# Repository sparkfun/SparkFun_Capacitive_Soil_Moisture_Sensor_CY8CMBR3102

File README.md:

[*SparkFun Qwiic Soil Moisture Sensor (Capacitive) (SEN-30480)*](https://www.sparkfun.com/sparkfun-qwiic-soil-moisture-sensor-capacitive.html)

The SparkFun Qwiic Soil Moisture Sensor (Capacative) is a simple sensor breakout to measure moisture in soil and similar substances. The breakout measures moisture using a capacitive plate in the board along with the CY8CMBR3102 Capsense<sup>&reg;</sup> Express<sup>&trade;</sup> controller. Because this soil moisture sensor does not have exposed metal leads it's more resistant to corrosion. The board also includes a ruler with both Imperial and Metric units to measure the sensor's depth in soil for more precise moisture data. There's also a blue status LED tied to the CY8CMBR3102 which can be used as a visual indicator for when the sensor measures beyond a user-defined threshold value.

The SparkFun Qwiic Soil Moisture Sensor (Capacative) has code packages available for both the Arduino IDE and MicroPython. These code packages cover how to calibrate the sensor for different soil compositions to get reliable and usable soil moisture data from the sensor.

Repository Contents
-------------------

* **/docs** - GitHub pages documentation files
* **/Documentation** - Datasheets, etc. 
* **/Hardware** - KiCad design files (_pcb, _sch), Schematic (PDF)
* **/Production** - Production panel files (_pcb, gerbers)

Documentation
--------------
* [**Arduino Library**](https://github.com/sparkfun/SparkFun_CY8CMBR3_Arduino_Library) - Arduino library for CY8CMBR3xxx capacitance sensors, specifically for the Qwiic Soil Moisture Sensor (Capacitive).
* [**Python Package**](https://github.com/sparkfun/qwiic_cy8cmbr3_py) - A Python driver for CY8CMBR3xxx capacitance sensors, specifically for the Qwiic Soil Moisture Sensor (Capacitive).
* [**Hookup Guide**](https://docs.sparkfun.com/SparkFun_Capacitive_Soil_Moisture_Sensor_CY8CMBR3102/introduction/) - A basic guide to get started with the Qwiic Soil Moisture Sensor (Capacitive)

Product Versions
-----------------

* [SEN-30480](https://www.sparkfun.com/sparkfun-qwiic-soil-moisture-sensor-capacitive.html) - Initial SparkFun Qwiic Soil Moisture Sensor (Capacitive) release.

License Information
-------------------

This product is _**open source**_! 

Please review the LICENSE.md file for license information. 

If you have any questions or concerns on licensing, please contact technical support on our [SparkFun forums](https://forum.sparkfun.com/viewforum.php?f=152).

Distributed as-is; no warranty is given.

- Your friends at SparkFun.

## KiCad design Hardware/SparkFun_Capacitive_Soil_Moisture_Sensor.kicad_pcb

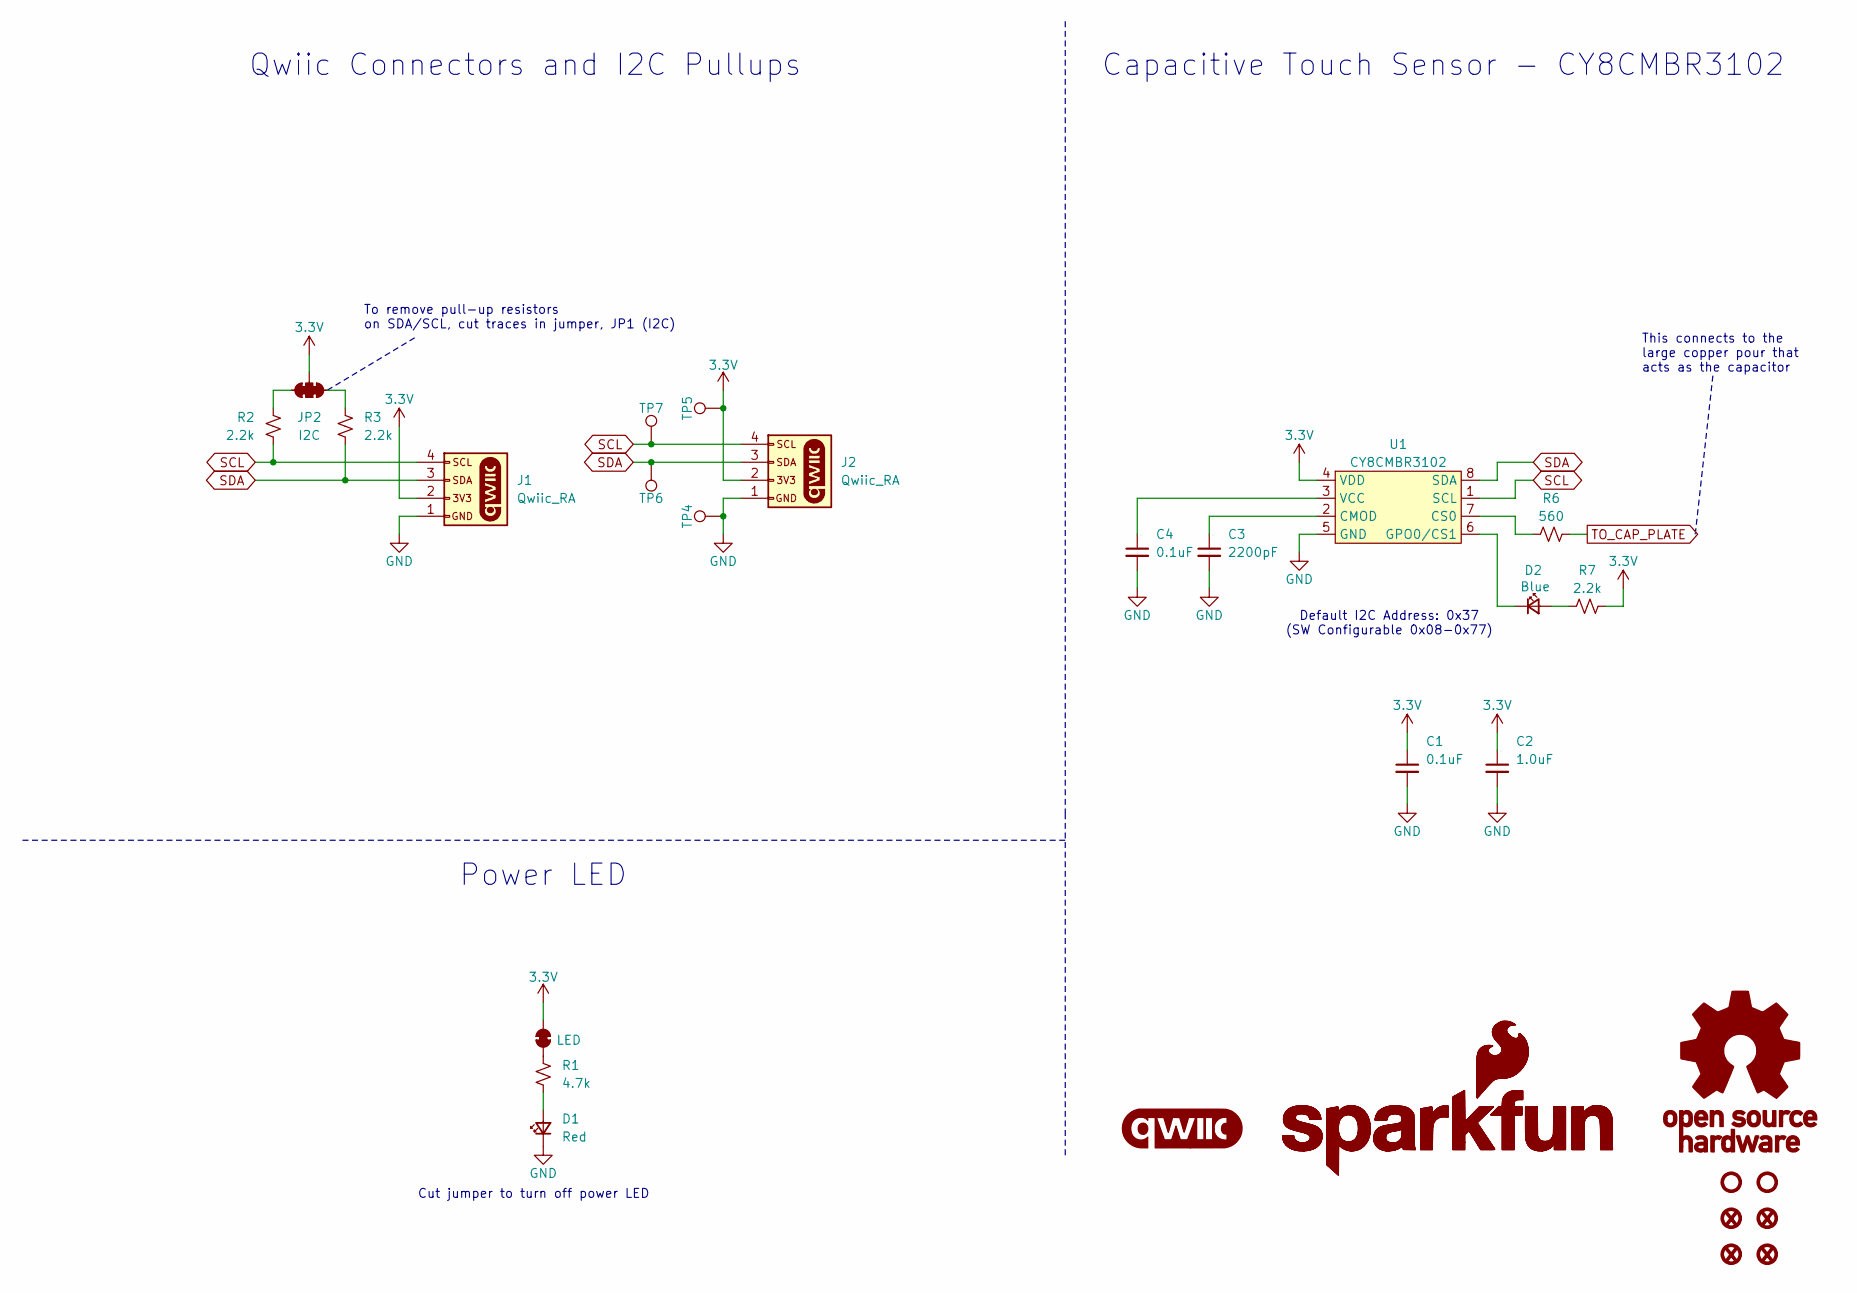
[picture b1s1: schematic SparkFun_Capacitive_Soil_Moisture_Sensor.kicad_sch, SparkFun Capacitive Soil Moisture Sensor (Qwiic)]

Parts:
C1, C4: 0.1uF; C_0603_1608Metric; Voltage 25V; Tolerance 20%
C2: 1.0uF; C_0603_1608Metric; Voltage 16V; Tolerance 10%
C3: 2200pF; C_0603_1608Metric; Voltage 50V; Tolerance 10%
D1: Red; LED_0603_1608Metric_Red
D2: Blue; LED_0603_1608Metric_Blue
FID1, FID2, FID3, FID4: Fiducial_0.5mm; Fiducial_0.5mm_Mask1mm
G1: SparkFun_Logo; SparkFun_Logo_8mm
G2: SparkFun_Logo
G3: OSHW_Logo; Creative_Commons_License
G4: qwiic_Logo
J1, J2: Qwiic_RA; JST_1x04_P1.0mm_Horizontal_SMD
JP1: LED; Jumper_2_NC_Trace
JP2: I2C; Jumper_3_NC-2_Trace
R1: 4.7k; R_0603_1608Metric
R2, R3, R7: 2.2k; R_0603_1608Metric
R6: 560; R_0603_1608Metric
ST2, ST4: Stand_off; Standoff
TP4, TP5, TP6, TP7: 1.0mm; TestPoint-1.0mm
U1: CY8CMBR3102; SO-8

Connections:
3.3V: C1.1, C2.1, J1.2, J2.2, JP1.2 (B), JP2.2 (B), R7.1, TP5.1, U1.4 (VDD)
GND: C1.2, C2.2, C3.2, C4.2, D1.1 (K), J1.1, J2.1, TP4.1, U1.5 (GND)
unnamed: D1.2 (A), R1.1
unnamed: D2.2 (A), R7.2
unnamed: D2.1 (K), U1.6 (GPO0/CS1)
unnamed: JP1.1 (A), R1.2
unnamed: JP2.1 (A), R3.1
unnamed: JP2.3 (C), R2.1
unnamed: C3.1, U1.2 (CMOD)
unnamed: R6.1, U1.7 (CS0)
unnamed: C4.1, U1.3 (VCC)
SCL: J1.4, J2.4, R2.2, TP7.1, U1.1 (SCL)
SDA: J1.3, J2.3, R3.2, TP6.1, U1.8 (SDA)
TO_CAP_PLATE: R6.2

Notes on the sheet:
Qwiic Connectors and I2C Pullups
Capacitive Touch Sensor - CY8CMBR3102
Cut jumper to turn off power LED
To remove pull-up resistors on SDA/SCL, cut traces in jumper, JP1 (I2C)
This connects to the large copper pour that acts as the capacitor
Power LED
Default I2C Address: 0x37 (SW Configurable 0x08-0x77)

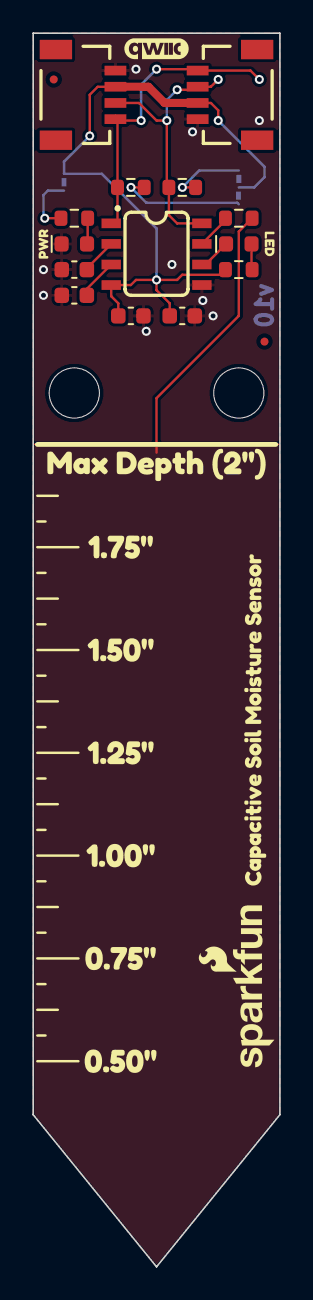
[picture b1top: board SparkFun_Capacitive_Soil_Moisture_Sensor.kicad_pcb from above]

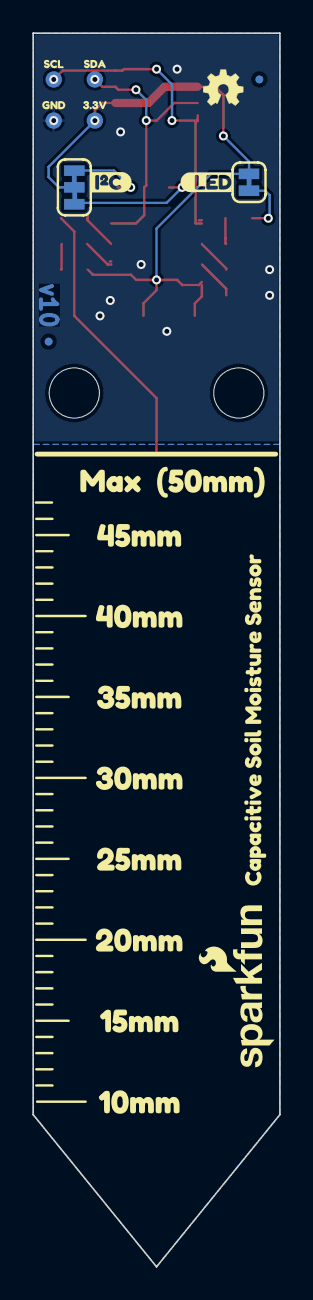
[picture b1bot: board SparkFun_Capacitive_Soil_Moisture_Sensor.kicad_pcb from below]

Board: 2 copper layers, 15.2 x 76.2 mm, 54 parts (25 on the bottom side), 13 nets.

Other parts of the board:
Ref**: Val**; OSHW_Logo_2.5mm
kibuzzard-693B565E, kibuzzard-693B565E#2: G***; kibuzzard-693B565E
kibuzzard-693C8DDA: G***; kibuzzard-693C8DDA
kibuzzard-693C8DE4: G***; kibuzzard-693C8DE4
kibuzzard-69334C1A: G***; kibuzzard-69334C1A
kibuzzard-69837BBB: G***; kibuzzard-69837BBB
kibuzzard-69837BD1: G***; kibuzzard-69837BD1
kibuzzard-69837BDA: G***; kibuzzard-69837BDA
kibuzzard-69837BE0: G***; kibuzzard-69837BE0
kibuzzard-69837BE5: G***; kibuzzard-69837BE5
kibuzzard-69837BE9: G***; kibuzzard-69837BE9
kibuzzard-69837BEE: G***; kibuzzard-69837BEE
kibuzzard-69837BF5: G***; kibuzzard-69837BF5
kibuzzard-693350BE: G***; kibuzzard-693350BE
kibuzzard-696937A1: G***; kibuzzard-696937A1
kibuzzard-696937A5: G***; kibuzzard-696937A5
kibuzzard-6937166E: G***; kibuzzard-6937166E
kibuzzard-6937167A: G***; kibuzzard-6937167A
kibuzzard-6969377A: G***; kibuzzard-6969377A
kibuzzard-6969378A: G***; kibuzzard-6969378A
kibuzzard-6969379D: G***; kibuzzard-6969379D
kibuzzard-6983799B: G***; kibuzzard-6983799B
kibuzzard-69371667: G***; kibuzzard-69371667
kibuzzard-69371675: G***; kibuzzard-69371675
kibuzzard-69693792: G***; kibuzzard-69693792
kibuzzard-69693797: G***; kibuzzard-69693797

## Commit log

2025-12-02 add .gitignore
2025-12-05 Add initial schematic and layout
2025-12-08 Cleanup test points and silkscreen, remove acid traps
2025-12-09 Make schematic updates from preliminary review
2025-12-11 Add functional changes to PCB from review.
    Achieves MVP, does not have all requested aesthetic changes.
2025-12-11 Update schematic with new cap sensing chip
2025-12-11 Add ruler to silkscreen on PCB
2025-12-12 Add schematic fixes from initial review
2025-12-12 Update PCB with new CY8CMBR3 IC
2025-12-15 Cleanup symmetry and add measurements
2025-12-17 Change repo name
2025-12-17 Fix sizing and naming in schematic based on review
2025-12-17 Add PCB fixes from review
2025-12-18 Create version of the PCB with components alligned to 12.5mil grid
2025-12-19 Update cap to correct prod_id
2026-01-15 Roll version for reds and increase silk font
2026-01-16 Adds Gerbers - waiting on parts
2026-01-22 Remove the 330 ohm series I2C resistors.
    These resistors cause issues when you daisy chain qwiic devices as they
    form a voltage divider with the pull-up resistance.
2026-02-04 Add changes from final review
2026-02-04 Add metric ruler
2026-02-04 Center max line
2026-02-24 Docs commit
    Initial docs commit. Including most content and files to prep for review & publish.
2026-02-25 Docs review update
    Final review updates. Adding README.md and GH pages build file.
2026-02-25 Update nav.html
    Removing Hard Copies link as it's redundant.
2026-02-25 Update tabs.html
    Removing Hard Copies tab from tabs.html
2026-02-26 Deployed 0361181 with MkDocs version: 1.6.1
2026-06-03 Deployed 5b595af with MkDocs version: 1.6.1

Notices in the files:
parts and their libraries:
https://creativecommons.org/licenses/by-sa/4.0
Released under the Creative Commons Attribution Share-Alike 4.0 License
